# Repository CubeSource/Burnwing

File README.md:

Burnwing is a burnwire development PCB. It is a engineering model to assist in the development of thermal knife release mechanisms and testing of deployables.

Powered by USB C with selectable current and voltage limits for easy testing or by picoblade/picolock connectors.
Default 5V, 1A 

https://www.cubesource.space/product-page/burnwire-release-mechanism

Additional Resources:
https://www.cubesource.space/resources
https://docs.google.com/spreadsheets/d/1-gqduE5_rplaJSyHokB8z7FWwOto8bMK/edit?usp=drive_link&ouid=104061366178972938101&rtpof=true&sd=true

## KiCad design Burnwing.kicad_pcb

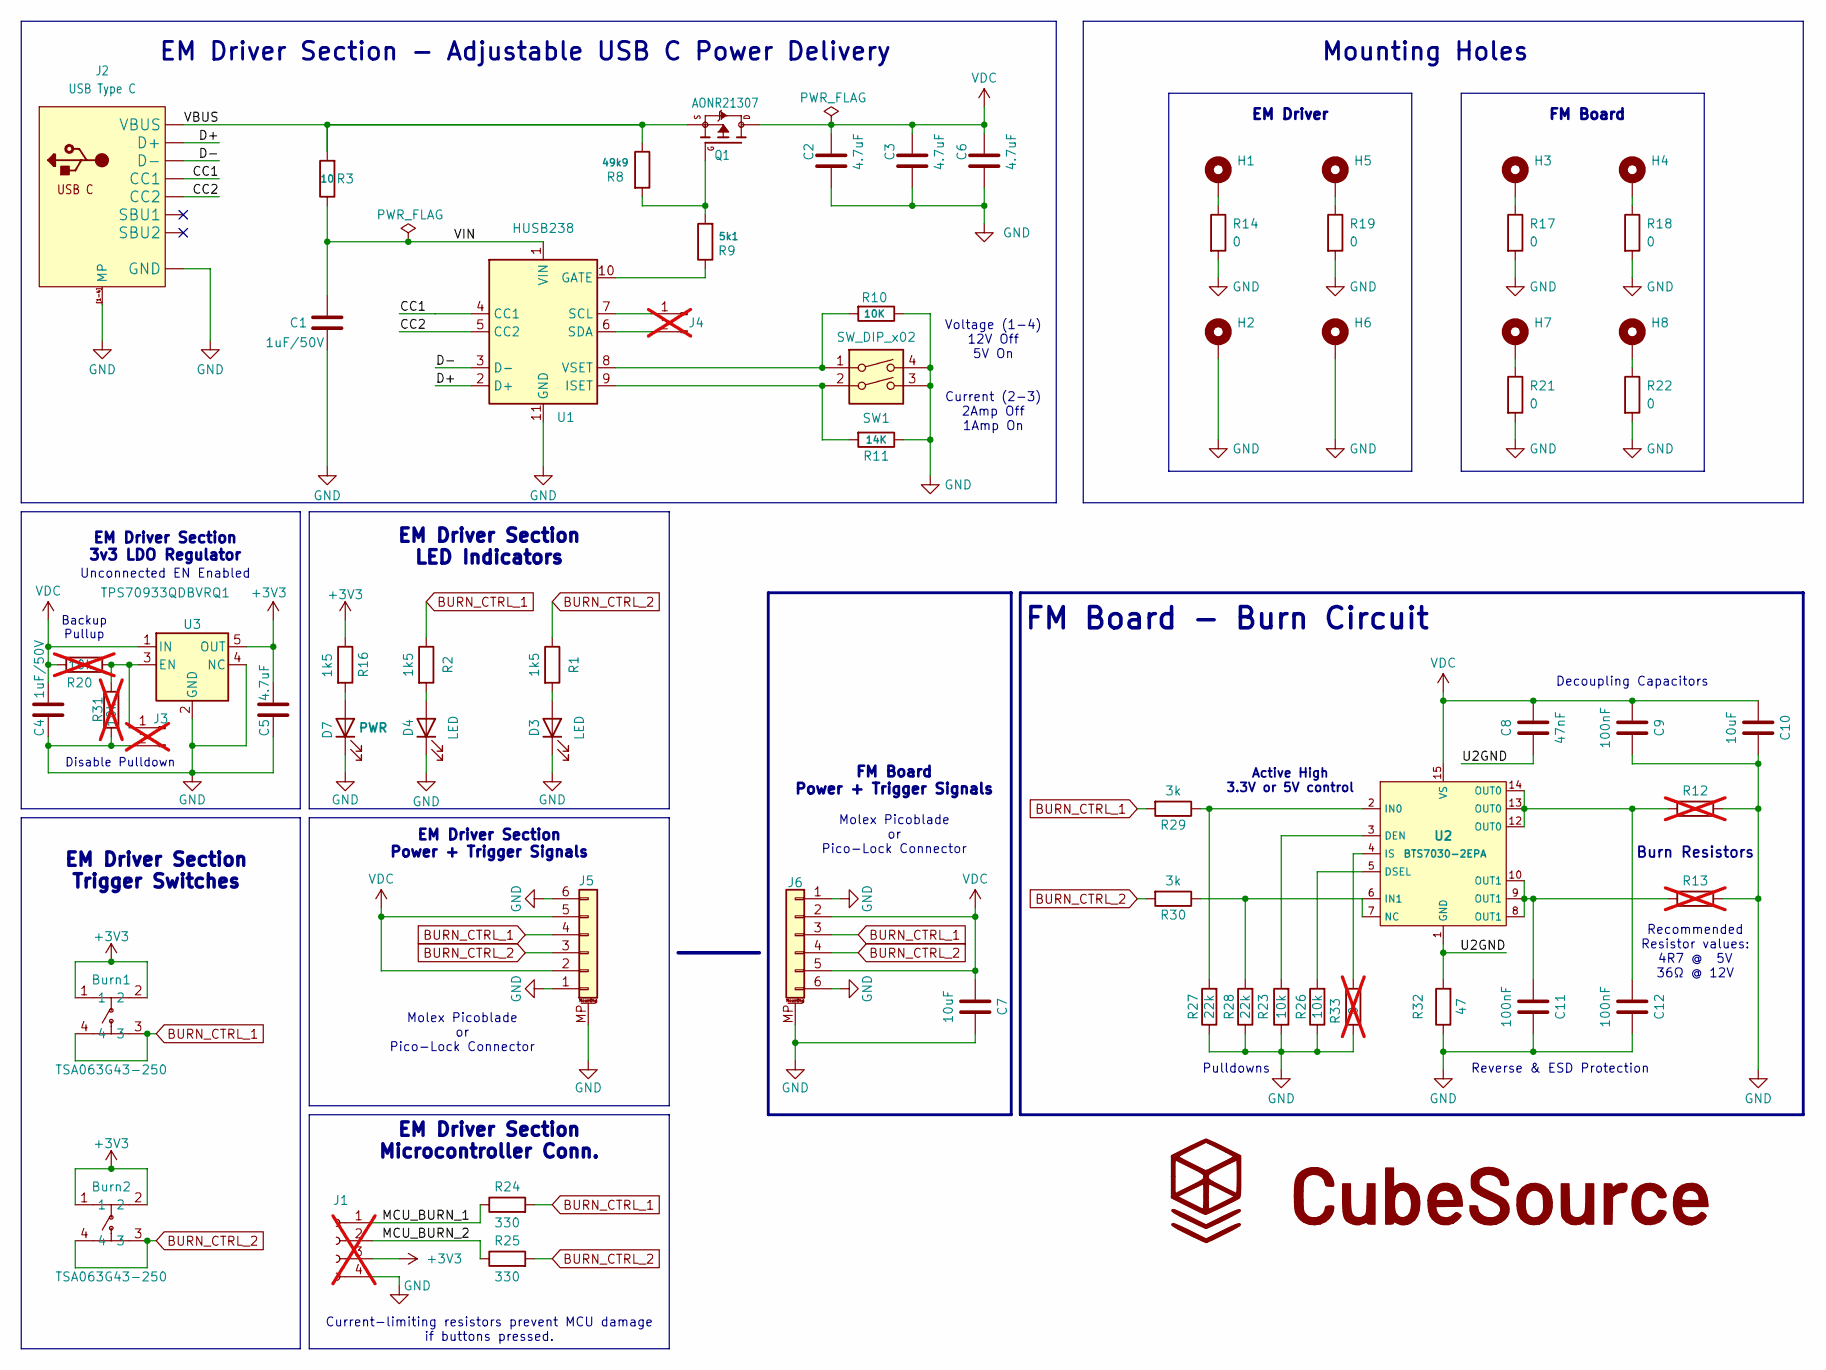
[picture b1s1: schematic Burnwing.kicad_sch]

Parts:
Burn1, Burn2: TSA063G43-250; KEY-SMD_4P-L6.0-W6.0-P4.50-LS10.0; MPN TSA063G43-250; LCSC Part C294564
C1, C4: 1uF/50V; C_0805_2012Metric_Pad1.18x1.45mm_HandSolder; LCSC C28323
C2, C3, C5, C6: 4.7uF; C_0805_2012Metric_Pad1.18x1.45mm_HandSolder; LCSC C437557
C7, C10: 10uF; C_0603_1608Metric_Pad1.08x0.95mm_HandSolder; LCSC C697423
C8: 47nF; C_0402_1005Metric_Pad0.74x0.62mm_HandSolder; LCSC C368599
C9, C11, C12: 100nF; C_0402_1005Metric_Pad0.74x0.62mm_HandSolder; LCSC C85858
D3, D4: LED; LED_0603_1608Metric_Pad1.05x0.95mm_HandSolder; LCSC C2286
D7: PWR; LED_0603_1608Metric_Pad1.05x0.95mm_HandSolder; LCSC C2286
H1, H3, H4, H5, H7, H8: MountingHole_Pad; MountingHole_2.2mm_M2_Pad
H2, H6: MountingHole_Pad; MountingHole_2.2mm_M2_Pad_4mm
J1: Conn_01x04_Socket; HDR-TH_4P-P2.54-V-F; not fitted
J2: USB Type C; USB-C-SMD_G-SWITCH_GT-USB-7010ASV; MPN GT-USB-7010ASV; LCSC C2988369
J3, J4: Conn_01x02_Pin; PinSocket_1x02_P1.27mm_Vertical; not fitted
J5: Conn_01x06_MountingPin; Molex_Pico-Lock_and_PicoBlade_Mirror; LCSC C563981
J6: Conn_01x06_MountingPin; Molex_Pico-Lock_and_PicoBlade; LCSC C563981
Q1: AONR21307; POWERDI3333; LCSC C3277813
R1, R2, R16: 1k5; R_0603_1608Metric_Pad0.98x0.95mm_HandSolder; LCSC C22843
R3: 10; R_0603_1608Metric_Pad0.98x0.95mm_HandSolder; LCSC C203240
R8: 49k9; R_0603_1608Metric_Pad0.98x0.95mm_HandSolder; LCSC C705780
R9: 5k1; R_0603_1608Metric_Pad0.98x0.95mm_HandSolder; LCSC C105580
R10: 10K; R_0603_1608Metric_Pad0.98x0.95mm_HandSolder; LCSC C116677
R11: 14K; R_0603_1608Metric_Pad0.98x0.95mm_HandSolder; LCSC C881028
R12, R13: R; AxialBurnResistor_No_Cutout; not fitted
R14, R19: 0; R_0603_1608Metric_Pad0.98x0.95mm_HandSolder; LCSC C100044
R17, R18, R21, R22: 0; R_0603_1608Metric_Pad0.98x0.95mm_HandSolder; LCSC C141796
R20, R31: 10k; R_0603_1608Metric_Pad0.98x0.95mm_HandSolder; not fitted
R23, R26: 10k; R_0603_1608Metric_Pad0.98x0.95mm_HandSolder; LCSC C116677
R24, R25: 330; R_0603_1608Metric_Pad0.98x0.95mm_HandSolder; LCSC C23138
R27, R28: 22k; R_0603_1608Metric_Pad0.98x0.95mm_HandSolder; LCSC C144680
R29, R30: 3k; R_0603_1608Metric_Pad0.98x0.95mm_HandSolder; LCSC C445829
R32: 47; R_0603_1608Metric_Pad0.98x0.95mm_HandSolder; LCSC C144656
R33: 0; R_0402_1005Metric_Pad0.72x0.64mm_HandSolder; LCSC C141796; not fitted
SW1: SW_DIP_x02; 2_Dipswitch; LCSC C7430304
U1: HUSB238; WDFN-10-1EP_3x3mm_P0.5mm_EP1.8x2.5mm; LCSC C7471904
U2: BTS7030-2EPA; PG-TSDSO-14_L4.9-W3.9-P0.65-LS6.0-BL-EP; LCSC Part C534836
U3: TPS70933QDBVRQ1; SOT-23-5; LCSC C90991

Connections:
+3V3: Burn1.1, Burn1.2, Burn2.1, Burn2.2, C5.1, J1.3, R16.1, U3.5 (OUT)
/CC1: J2.A5 (CC1), U1.4 (CC1)
/CC2: J2.B5 (CC2), U1.5 (CC2)
/D+: J2.A6 (D+), J2.B6 (D+), U1.2 (D+)
/D-: J2.A7 (D-), J2.B7 (D-), U1.3 (D-)
/MCU_BURN_1: J1.1, R24.1
/MCU_BURN_2: J1.2, R25.1
/U2GND: C8.2, R32.2, U2.1 (GND)
/VBUS: J2.A4B9 (VBUS), J2.B4A9 (VBUS), Q1.1 (S), Q1.2 (S), Q1.3 (S), R3.2, R8.1
/VIN: C1.1, R3.1, U1.1 (VIN)
BURN_CTRL_1: Burn1.3, Burn1.4, J5.4, J6.3, R2.1, R24.2, R29.2
BURN_CTRL_2: Burn2.3, Burn2.4, J5.3, J6.4, R1.1, R25.2, R30.2
GND: C1.2, C2.2, C3.2, C4.2, C5.2, C6.2, C7.2, C9.1, C10.1, C11.2, C12.1, D3.1 (K), D4.1 (K), D7.1 (K), H2.1 (1_1), H6.1 (1_1), J1.4, J2.1 (MP), J2.2 (MP), J2.3 (MP), J2.4 (MP), J2.A1B12 (GND), J2.B1A12 (GND), J2.[1-4] (MP), J3.2, J5.1, J5.6, J5.MP (MountPin), J6.1, J6.6, J6.MP (MountPin), R10.1, R11.1, R12.1, R13.1, R14.2, R17.2, R18.2, R19.2, R21.2, R22.2, R23.1, R26.1, R27.1, R28.1, R31.2, R32.1, R33.1, SW1.3, SW1.4, U1.11 (GND), U3.2 (GND), U3.4 (NC); also elsewhere on the board
unnamed 13: C11.1, R13.2, U2.8 (OUT1), U2.9 (OUT1), U2.10 (OUT1); also elsewhere on the board
unnamed 14: C12.2, R12.2, U2.12 (OUT0), U2.13 (OUT0), U2.14 (OUT0); also elsewhere on the board
unnamed: D3.2 (A), R1.2
unnamed: D4.2 (A), R2.2
unnamed: D7.2 (A), R16.2
unnamed: H1.1 (1_1), R14.1
unnamed: H3.1 (1_1), R17.1
unnamed: H4.1 (1_1), R18.1
unnamed: H5.1 (1_1), R19.1
unnamed: H7.1 (1_1), R21.1
unnamed: H8.1 (1_1), R22.1
unnamed: J3.1, R20.2, R31.1, U3.3 (EN)
unnamed: J4.1, U1.7 (SCL)
unnamed: J4.2, U1.6 (SDA)
unnamed: Q1.4 (G), R8.2, R9.2
unnamed: R9.1, U1.10 (GATE)
unnamed: R11.2, SW1.2, U1.9 (ISET)
unnamed: R10.2, SW1.1, U1.8 (VSET)
unnamed: R23.2, U2.3 (DEN)
unnamed: R26.2, U2.5 (DSEL)
unnamed: R27.2, R29.1, U2.2 (IN0)
unnamed: R28.2, R30.1, U2.6 (IN1), U2.7 (NC)
unnamed: R33.2, U2.4 (IS)
VDC: C2.1, C3.1, C4.1, C6.1, C7.1, C8.1, C9.2, C10.2, J5.2, J5.5, J6.2, J6.5, Q1.5678 (D), R20.1, U2.15 (VS), U3.1 (IN)

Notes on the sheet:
FM Board Power + Trigger Signals
FM Board
Mounting Holes
EM Driver Section 3v3 LDO Regulator
Reverse & ESD Protection
EM Driver Section LED Indicators
EM Driver Section - Adjustable USB C Power Delivery
Pulldowns
FM Board - Burn Circuit
Molex Picoblade or Pico-Lock Connector
Recommended Resistor values: 4R7 @ 5V 36Ω @ 12V
Decoupling Capacitors
EM Driver Section Power + Trigger Signals
EM Driver Section Trigger Switches
Voltage (1-4) 12V Off 5V On
Burn Resistors
Unconnected EN Enabled
Current (2-3) 2Amp Off 1Amp On
Current-limiting resistors prevent MCU damage if buttons pressed.
Disable Pulldown
Active High 3.3V or 5V control
EM Driver Section Microcontroller Conn.
Backup Pullup
EM Driver

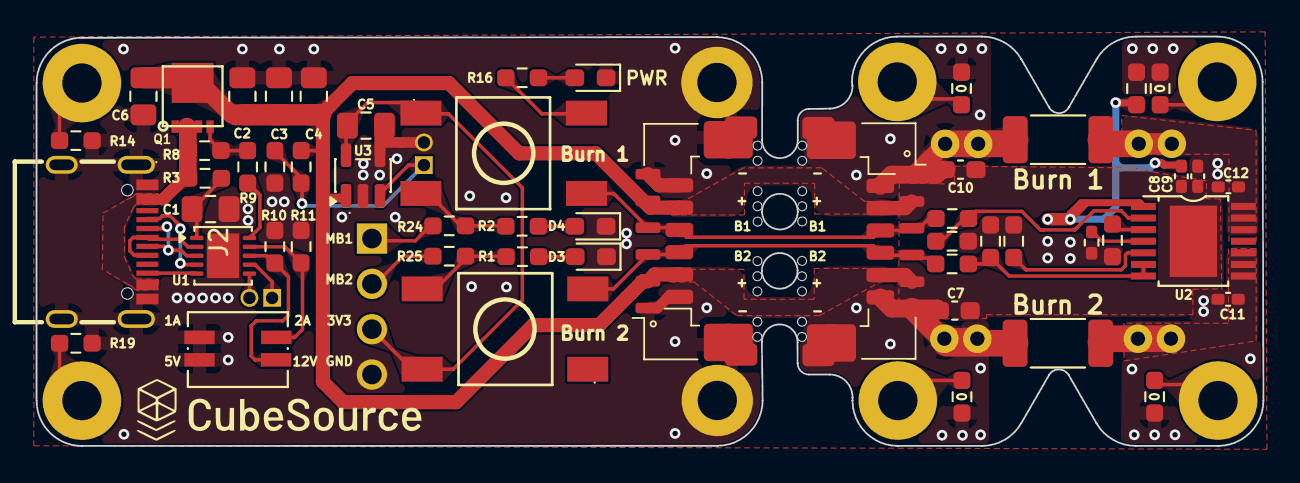
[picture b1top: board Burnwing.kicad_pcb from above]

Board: 2 copper layers, 68.7 x 22.9 mm, 68 parts (1 on the bottom side), 37 nets.

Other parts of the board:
.space, .space#2: LOGO; CubeSource
Burn 1, Burn 2: R_2010_5025Metric_Pad1.40x2.65mm_HandSolder

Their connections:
GND: Burn 1.1, Burn 2.1; also elsewhere on the board
unnamed 13: Burn 2.2; also elsewhere on the board
unnamed 14: Burn 1.2; also elsewhere on the board

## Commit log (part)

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2025-05-18 Initial upload
    Reupload of Rev1 to begin Rev2 updates
2025-05-18 Update README.md
    Added pictures
2025-06-22 Changed to USB C power
    Switched our regulator for selectable usb C power delivery
2025-06-22 Updated Schematic
2025-06-23 updated layou/schematic
2025-06-23 Routing updates
2025-06-26 Minor updates
2025-07-02 Cleaned up Schematic and exported project libraries
2025-07-02 fixed embedded models
2025-07-14 Changed PCB Layout
    Miniaturized PCB and removed any non flight components. Still need to update schematic.
2025-07-18 Reworked the layout
2025-07-18 Layout completed
2025-07-18 Cleaned schematic a bit
2025-07-19 Reworked usb power and cleaned up layout
2025-07-19 Update README.md
    New pics
2025-07-22 Make some traces widers and added decals
    Increased Trace width near R1 and R2 thru holes.
    Also added decals
2025-07-22 Added vias and cleaned up traces
2025-07-22 Cleaned up files and added part numbers
    Updated Schematics
    Updated STEP files
    Regenerated Project Libraries
    Added Part Numbers
2025-07-22 Added Decals and Labels
2025-07-23 Added Labels and removed unused files
2025-09-21 July Changes
2025-11-17 4 layer v3 template
2025-11-26 added dip switch
    add dip switch and adjusted layout a bit
2025-11-26 Library Fix
2025-11-26 google drive upload
2025-11-26 remove uneeded stuff
2025-11-29 updated CAD
2025-12-22 Separated Version
    -Added dipswitch for Vset and Iset
    -Added tentative microcontroller and jumper pins
    -Separated flight and not flight modes
    -Removed SCL/SDA
2025-12-22 Schematic Update
2026-01-04 Fixed Vias Issues
2026-01-04 QR Code Shifting
    Moved Jumper 2, QR Code, CubeSource link, and Burnwing Rev2
2026-01-05 fixing traces/vias
2026-01-05 Fixed VDC traces
2026-01-05 Changed jumper headers
    Changed jumper pins to 1.27 size
2026-01-05 VBUS Trace width fix
2026-01-06 Removed micro burn resistors
    Removed micro burn resistors and cleaned up layout. Swapped micro pin holes to 2.54 and cleaned up layout.
2026-01-06 updated dates
2026-03-07 Add additional resource link to README
2026-03-07 Update README with new satellite deployables info
2026-06-12 breakaway burnwing mini
    Form factor changes
2026-06-12 file cleanup
2026-06-13 library cleanup
2026-06-14 2layer rework
2026-06-24 pre ai save
2026-06-30 Revise README for Burnwing Mini Flight
    Updated project description and images for clarity.
2026-06-30 Fix formatting issues in README.md
2026-06-30 Fix punctuation in README description
    Added a period at the end of the description sentence.
